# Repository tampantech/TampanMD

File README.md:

# TampanMD
this is my first motor driver design

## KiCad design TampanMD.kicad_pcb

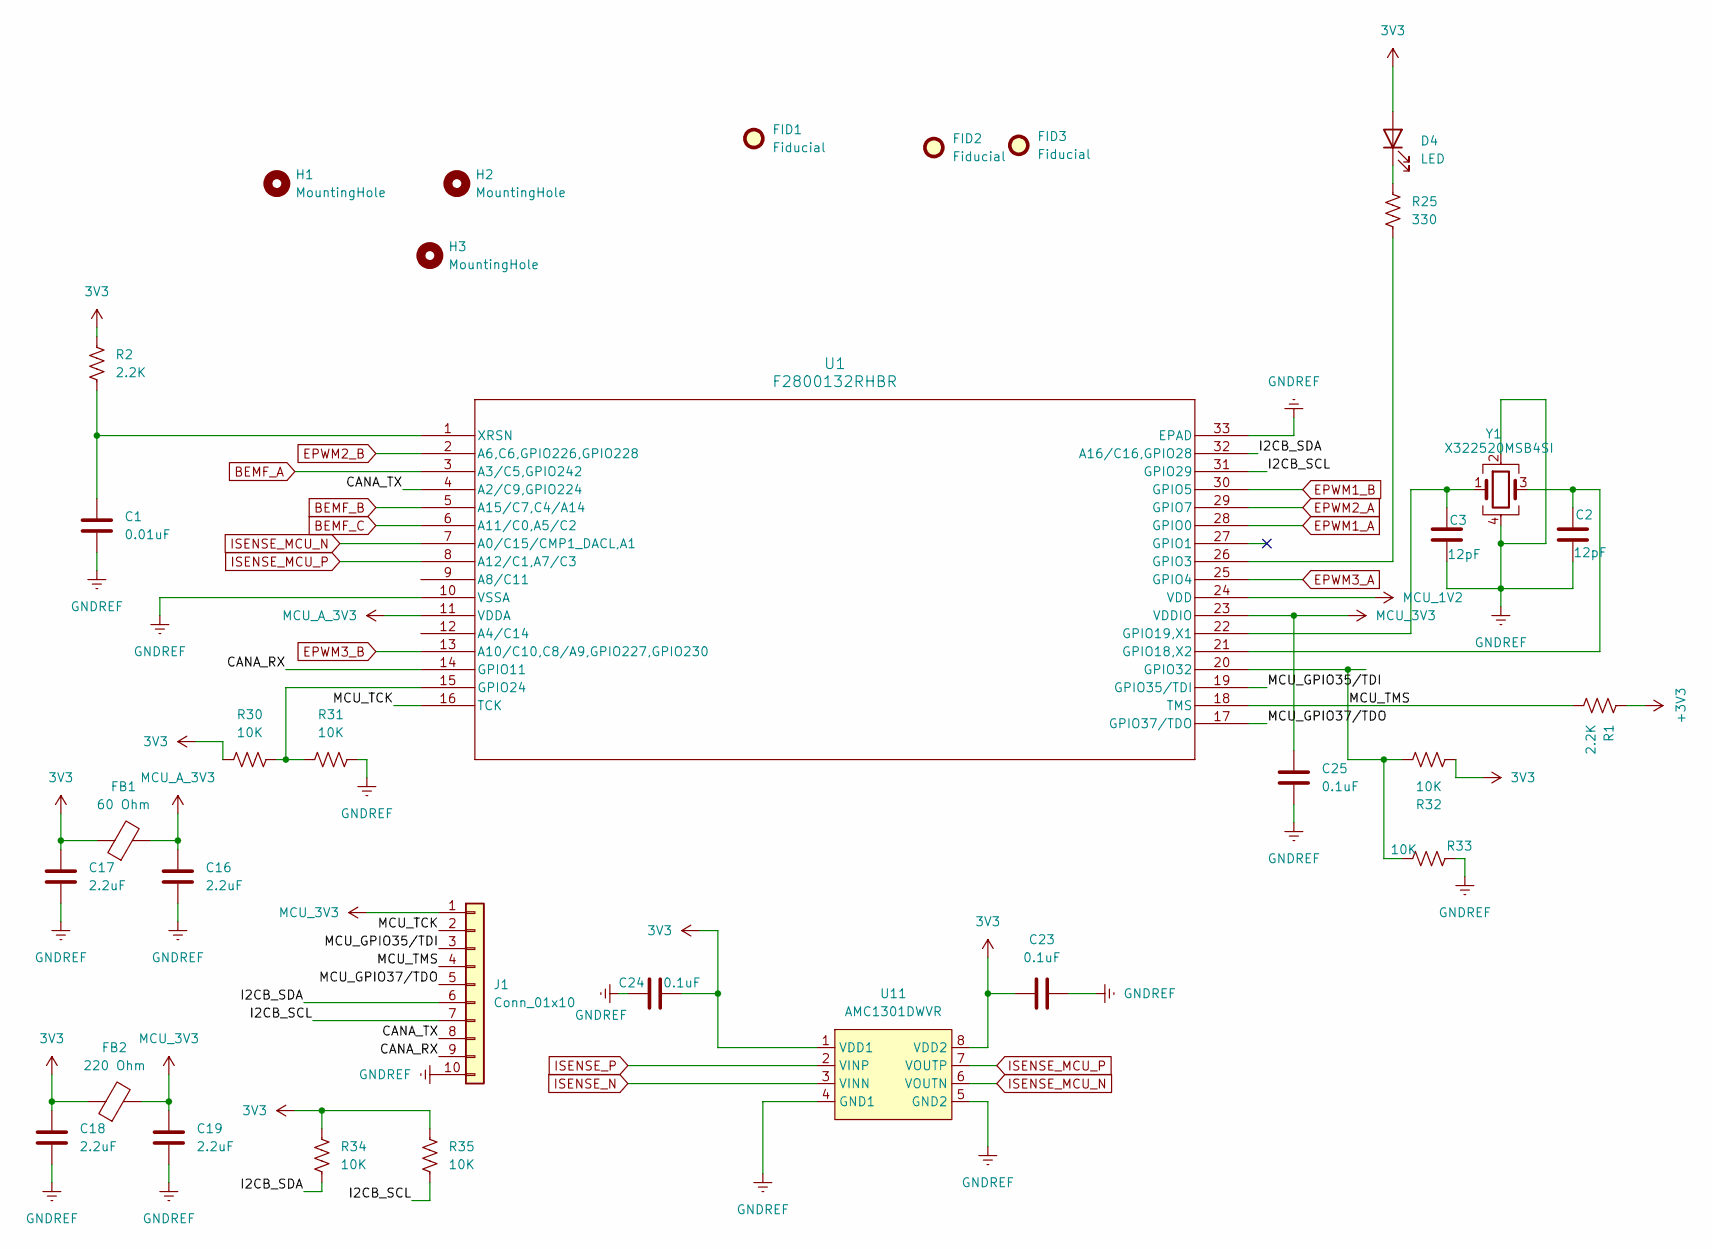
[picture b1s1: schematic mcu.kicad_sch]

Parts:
C1: 0.01uF; C_0402_1005Metric; LCSC Part # C106199
C2, C3: 12pF; C_0402_1005Metric; LCSC Part # C76948
C16, C17, C18, C19: 2.2uF; C_0805_2012Metric; LCSC Part # C2981733
C23, C24: 0.1uF; C_0603_1608Metric; LCSC Part # C14663
C25: 0.1uF; C_0402_1005Metric; LCSC Part # C77020
D4: LED; LED_0402_1005Metric; LCSC Part # C20608784
FB1: 60 Ohm; L_0603_1608Metric; LCSC Part # C85834
FB2: 220 Ohm; L_0805_2012Metric; LCSC Part # C85840
FID1, FID2, FID3: Fiducial; Fiducial_0.5mm_Mask1mm
H1, H2, H3: MountingHole; MountingHole_2.2mm_M2
J1: Conn_01x10; PinSocket_1x10_P2.54mm_Vertical
R1, R2: 2.2K; R_0603_1608Metric; LCSC Part # C114662
R25: 330; R_0402_1005Metric; LCSC Part # C105875
R30, R31, R32, R33, R34, R35: 10K; R_0603_1608Metric; LCSC Part # C98220
U1: F2800132RHBR; VQFN32_RHB_TEX
U11: AMC1301DWVR; SOIC-8_L5.9-W7.5-P1.27-LS11.5-BL; LCSC Part # C190273
Y1: X322520MSB4SI; CRYSTAL-SMD_4P-L3.2-W2.5-BL; LCSC Part # C9004

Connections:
3V3: C17.1, C18.1, C23.1, C24.1, D4.2 (A), FB1.1, FB2.1, R2.1, R30.1, R32.1, R34.1, R35.1, U11.1 (VDD1), U11.8 (VDD2); also elsewhere on the board
+3V3: R1.1
/MCU/CANA_RX: J1.9, U1.14 (GPIO11)
/MCU/CANA_TX: J1.8, U1.4 (A2/C9,GPIO224)
/MCU/I2CB_SCL: J1.7, R35.2, U1.31 (GPIO29)
/MCU/I2CB_SDA: J1.6, R34.2, U1.32 (A16/C16,GPIO28)
/MCU/MCU_GPIO35/TDI: J1.3, U1.19 (GPIO35/TDI)
/MCU/MCU_GPIO37/TDO: J1.5, U1.17 (GPIO37/TDO)
/MCU/MCU_TCK: J1.2, U1.16 (TCK)
/MCU/MCU_TMS: J1.4, R1.2, U1.18 (TMS)
BEMF_A: U1.3 (A3/C5,GPIO242); also elsewhere on the board
BEMF_B: U1.5 (A15/C7,C4/A14); also elsewhere on the board
BEMF_C: U1.6 (A11/C0,A5/C2); also elsewhere on the board
EPWM1_A: U1.28 (GPIO0); also elsewhere on the board
EPWM1_B: U1.30 (GPIO5); also elsewhere on the board
EPWM2_A: U1.29 (GPIO7); also elsewhere on the board
EPWM2_B: U1.2 (A6,C6,GPIO226,GPIO228); also elsewhere on the board
EPWM3_A: U1.25 (GPIO4); also elsewhere on the board
EPWM3_B: U1.13 (A10/C10,C8/A9,GPIO227,GPIO230); also elsewhere on the board
ISENSE_MCU_N: U1.7 (A0/C15/CMP1_DACL,A1), U11.6 (VOUTN)
ISENSE_MCU_P: U1.8 (A12/C1,A7/C3), U11.7 (VOUTP)
ISENSE_N: C1.2, C2.2, C3.2, C16.2, C17.2, C18.2, C19.2, C23.2, C24.2, C25.2, J1.10, R31.2, R33.2, U1.10 (VSSA), U1.33 (EPAD), U11.3 (VINN), U11.4 (GND1), U11.5 (GND2), Y1.2, Y1.4; also elsewhere on the board
ISENSE_P: U11.2 (VINP); also elsewhere on the board
MCU_1V2: U1.24 (VDD)
MCU_3V3: C19.1, C25.1, FB2.2, J1.1, U1.23 (VDDIO)
MCU_A_3V3: C16.1, FB1.2, U1.11 (VDDA)
unnamed: D4.1 (K), R25.1
unnamed: R25.2, U1.26 (GPIO3)
unnamed: C2.1, U1.21 (GPIO18,X2), Y1.3
unnamed: C3.1, U1.22 (GPIO19,X1), Y1.1
unnamed: R30.2, R31.1, U1.15 (GPIO24)
unnamed: R32.2, R33.1, U1.20 (GPIO32)
unnamed: C1.1, R2.2, U1.1 (XRSN)

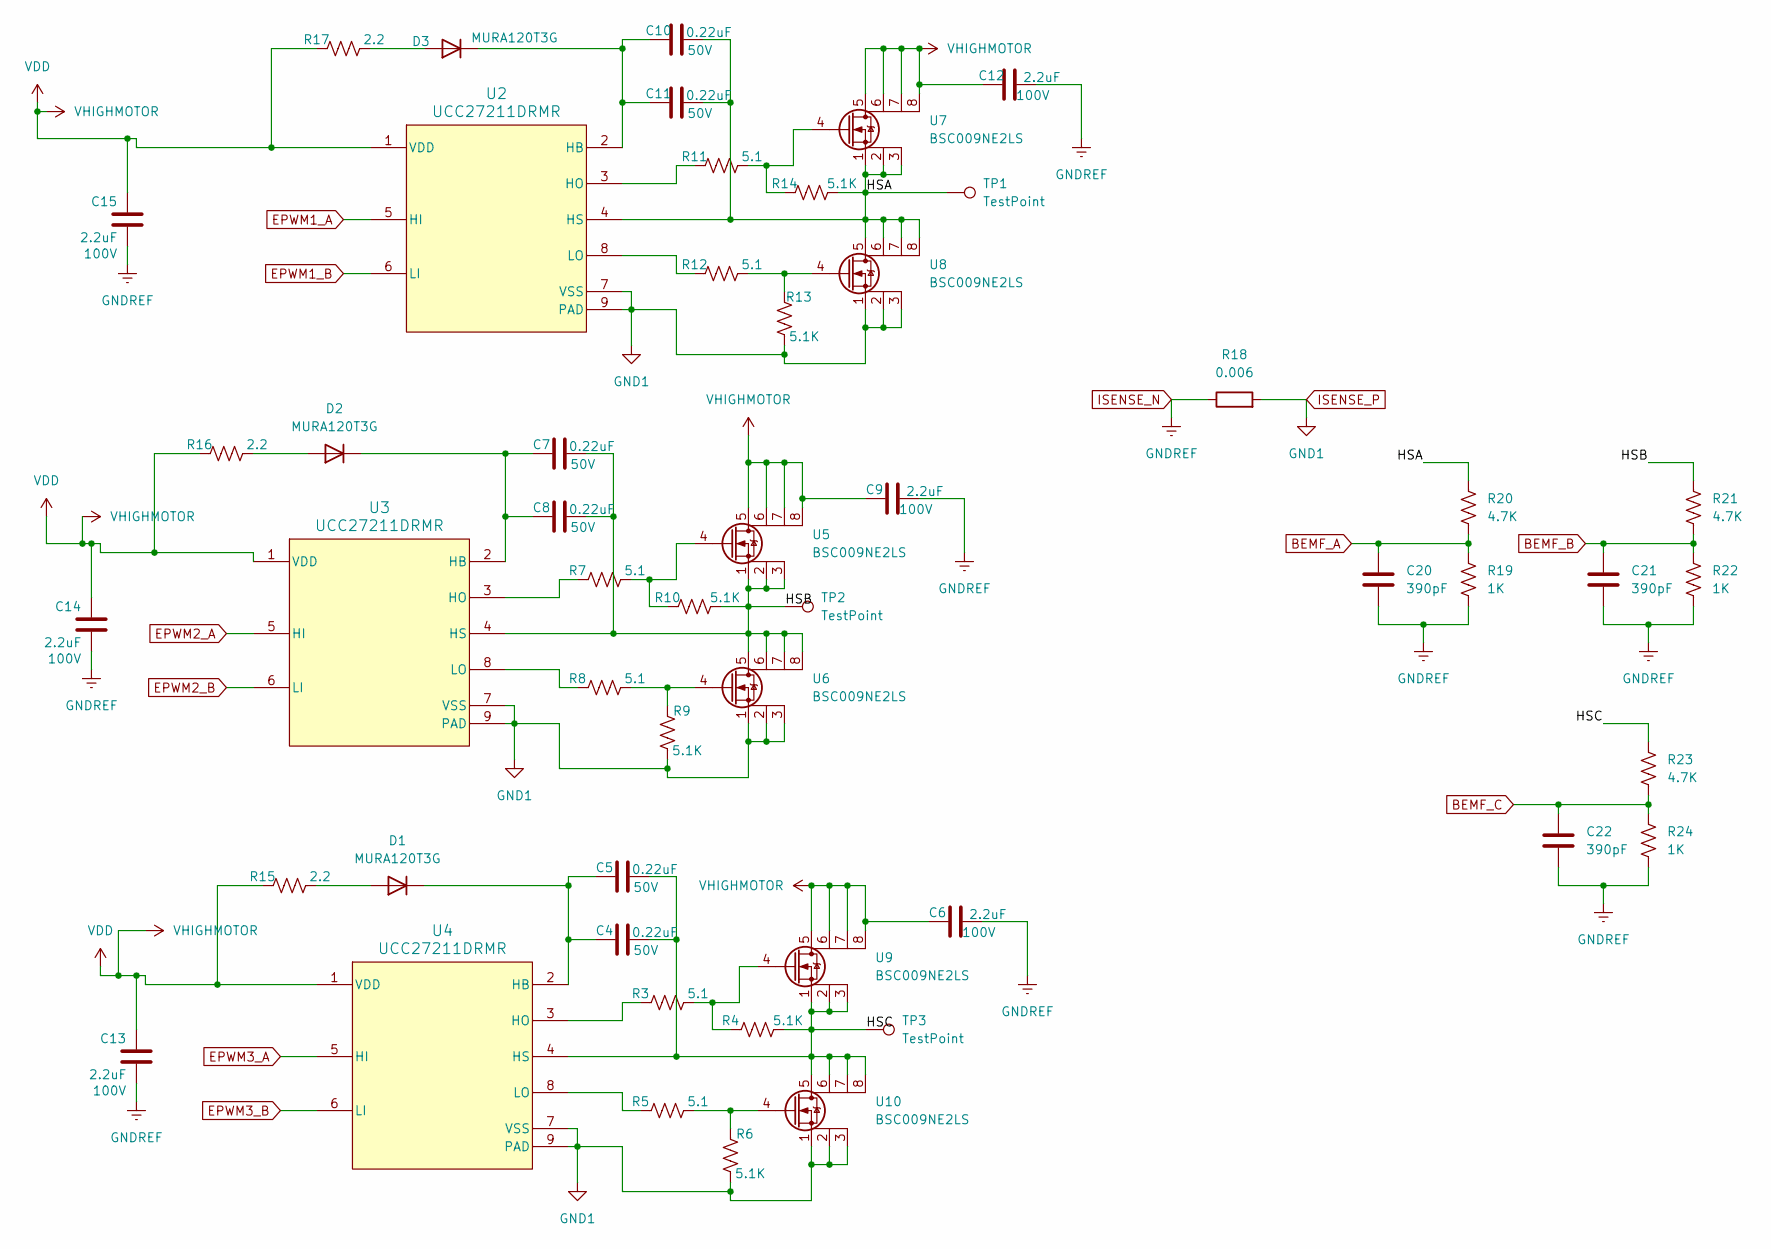
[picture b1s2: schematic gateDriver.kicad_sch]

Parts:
C4, C5, C7, C8, C10, C11: 0.22uF; C_0402_1005Metric; Voltage Rating 50V; LCSC Part # C16772
C6, C9, C12, C13, C14, C15: 2.2uF; C_0805_2012Metric; Voltage Rating 100V; LCSC Part # C2981733
C20, C21, C22: 390pF; C_0603_1608Metric; LCSC Part # C107050
D1, D2, D3: MURA120T3G; SMA_L4.3-W2.6-LS5.2-RD; LCSC Part # C7503111
R3, R5, R7, R8, R11, R12: 5.1; R_0603_1608Metric; LCSC Part # C25197
R4, R6, R9, R10, R13, R14: 5.1K; R_0603_1608Metric; LCSC Part # C2907044
R15, R16, R17: 2.2; R_0603_1608Metric; LCSC Part # C144672
R18: 0.006; R_0805_2012Metric; LCSC Part # C728268
R19, R22, R24: 1K; R_0603_1608Metric; LCSC Part # C22548
R20, R21, R23: 4.7K; R_0603_1608Metric; LCSC Part # C99782
TP1, TP2, TP3: TestPoint; MountingHole_2.5mm_Pad_TopBottom
U2, U3, U4: UCC27211DRMR; DRM0008A; LCSC Part # C544677
U5, U6, U7, U8, U9, U10: BSC009NE2LS; PG-TDSON-8_L5.0-W6.0-P1.27-BL-EP; LCSC Part # C534276

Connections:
/gateDriver/HSA: C10.2, C11.2, R14.1, R20.1, TP1.1, U2.4 (HS), U7.1, U7.2, U7.3, U8.5, U8.6, U8.7, U8.8
/gateDriver/HSB: C7.2, C8.2, R10.1, R21.1, TP2.1, U3.4 (HS), U5.1, U5.2, U5.3, U6.5, U6.6, U6.7, U6.8
/gateDriver/HSC: C4.2, C5.2, R4.1, R23.1, TP3.1, U4.4 (HS), U9.1, U9.2, U9.3, U10.5, U10.6, U10.7, U10.8
BEMF_A: C20.1, R19.1, R20.2; also elsewhere on the board
BEMF_B: C21.1, R21.2, R22.1; also elsewhere on the board
BEMF_C: C22.1, R23.2, R24.1; also elsewhere on the board
EPWM1_A: U2.5 (HI); also elsewhere on the board
EPWM1_B: U2.6 (LI); also elsewhere on the board
EPWM2_A: U3.5 (HI); also elsewhere on the board
EPWM2_B: U3.6 (LI); also elsewhere on the board
EPWM3_A: U4.5 (HI); also elsewhere on the board
EPWM3_B: U4.6 (LI); also elsewhere on the board
ISENSE_N: C6.2, C9.2, C12.2, C13.1, C14.1, C15.1, C20.2, C21.2, C22.2, R18.1, R19.2, R22.2, R24.2; also elsewhere on the board
ISENSE_P: R6.1, R9.1, R13.1, R18.2, U2.7 (VSS), U2.9 (PAD), U3.7 (VSS), U3.9 (PAD), U4.7 (VSS), U4.9 (PAD), U6.1, U6.2, U6.3, U8.1, U8.2, U8.3, U10.1, U10.2, U10.3; also elsewhere on the board
unnamed: D1.2 (A), R15.1
unnamed: C4.1, C5.1, D1.1 (K), U4.2 (HB)
unnamed: D2.2 (A), R16.1
unnamed: C7.1, C8.1, D2.1 (K), U3.2 (HB)
unnamed: D3.2 (A), R17.1
unnamed: C10.1, C11.1, D3.1 (K), U2.2 (HB)
unnamed: R3.1, R4.2, U9.4
unnamed: R5.1, R6.2, U10.4
unnamed: R8.1, R9.2, U6.4
unnamed: R7.1, R10.2, U5.4
unnamed: R11.1, R14.2, U7.4
unnamed: R12.1, R13.2, U8.4
unnamed: R11.2, U2.3 (HO)
unnamed: R12.2, U2.8 (LO)
unnamed: R7.2, U3.3 (HO)
unnamed: R8.2, U3.8 (LO)
unnamed: R3.2, U4.3 (HO)
unnamed: R5.2, U4.8 (LO)
VDD: C6.1, C9.1, C12.1, C13.2, C14.2, C15.2, R15.2, R16.2, R17.2, U2.1 (VDD), U3.1 (VDD), U4.1 (VDD), U5.5, U5.6, U5.7, U5.8, U7.5, U7.6, U7.7, U7.8, U9.5, U9.6, U9.7, U9.8; also elsewhere on the board

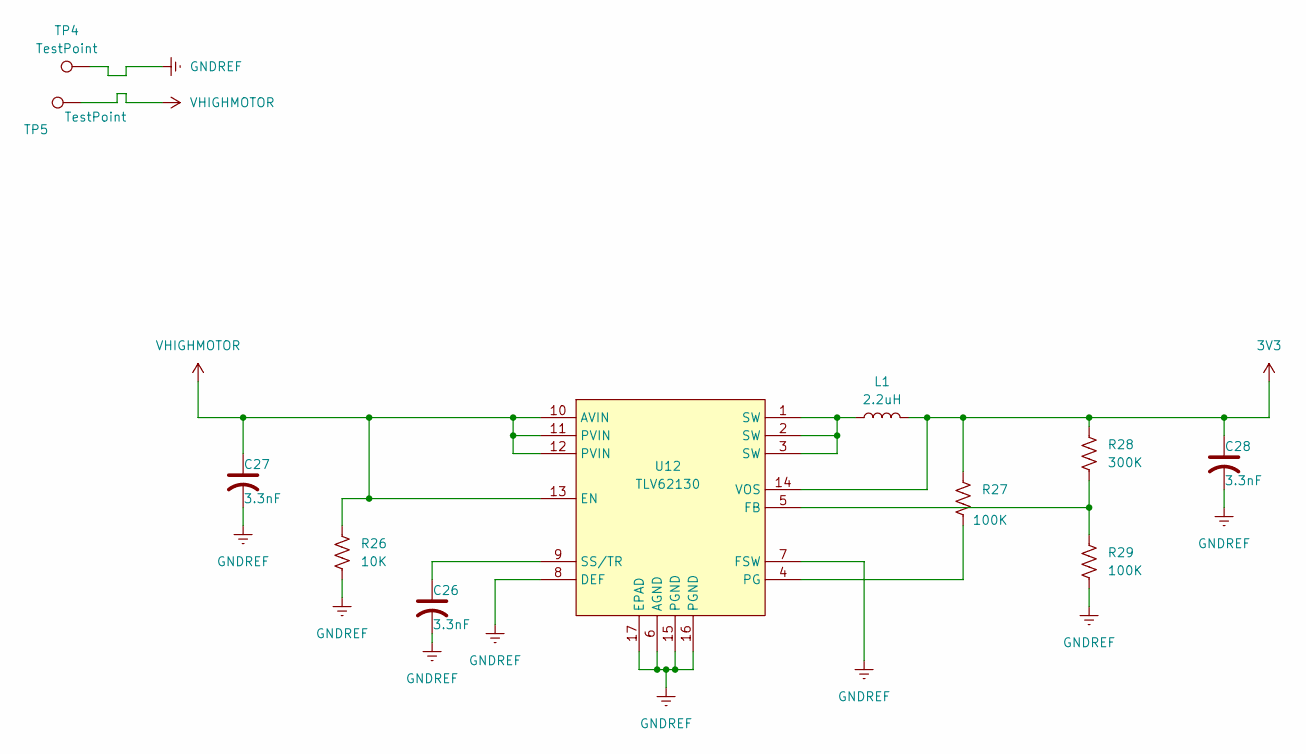
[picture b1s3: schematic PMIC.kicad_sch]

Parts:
C26, C27, C28: 3.3nF; C_0603_1608Metric; LCSC Part # C77036
L1: 2.2uH; L_0603_1608Metric; LCSC Part # C383369
R26: 10K; R_0402_1005Metric; LCSC Part # C60490
R27, R29: 100K; R_0402_1005Metric; LCSC Part # C60491
R28: 300K; R_0402_1005Metric; LCSC Part # C138011
TP4, TP5: TestPoint; MountingHole_2.5mm_Pad_TopBottom
U12: TLV62130; QFN-16_L3.0-W3.0-P0.50-TL-EP; LCSC Part # C122479

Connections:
3V3: C28.1, L1.2, R27.1, R28.1, U12.14 (VOS); also elsewhere on the board
ISENSE_N: C26.2, C27.2, C28.2, R26.2, R29.2, TP4.1, U12.6 (AGND), U12.7 (FSW), U12.8 (DEF), U12.15 (PGND), U12.16 (PGND), U12.17 (EPAD); also elsewhere on the board
unnamed: L1.1, U12.1 (SW), U12.2 (SW), U12.3 (SW)
unnamed: R28.2, R29.1, U12.5 (FB)
unnamed: R27.2, U12.4 (PG)
unnamed: C26.1, U12.9 (SS/TR)
VDD: C27.1, R26.1, TP5.1, U12.10 (AVIN), U12.11 (PVIN), U12.12 (PVIN), U12.13 (EN); also elsewhere on the board

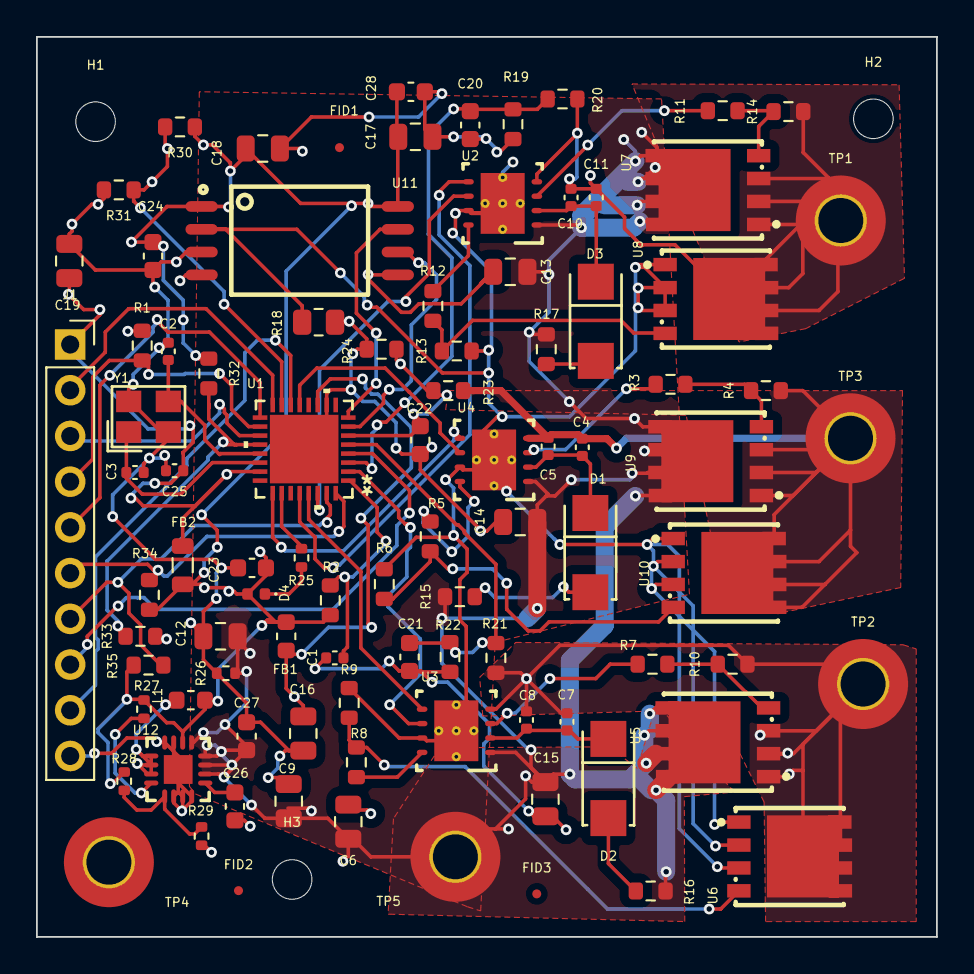
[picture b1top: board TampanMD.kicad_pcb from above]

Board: 2 copper layers, 50.0 x 50.0 mm, 95 parts (0 on the bottom side), 57 nets.

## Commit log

2025-11-01 done i guess
